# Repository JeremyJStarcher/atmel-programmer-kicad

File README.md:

# atmel-programmer-kicad
ATMEL AT programmer for 8, 14, 20 and 28pin DIP packages

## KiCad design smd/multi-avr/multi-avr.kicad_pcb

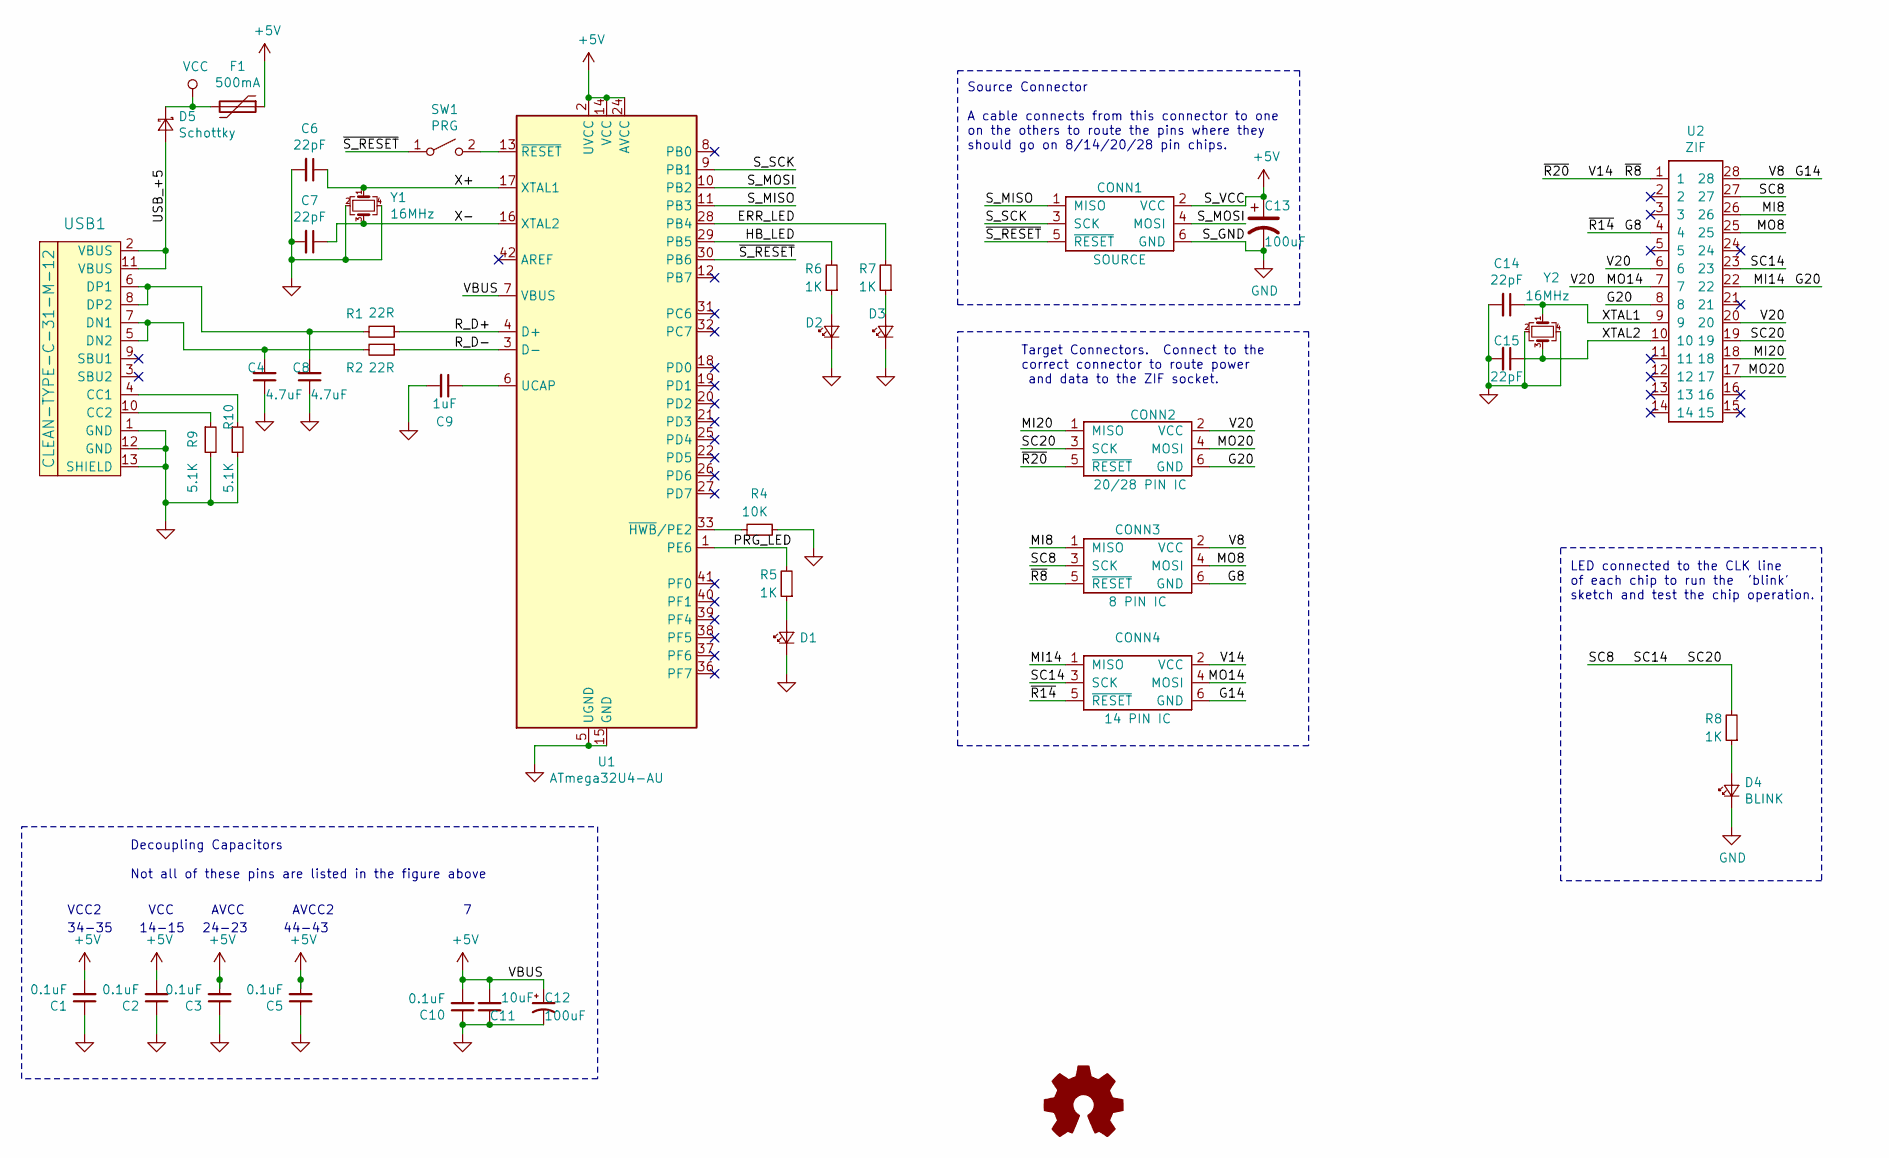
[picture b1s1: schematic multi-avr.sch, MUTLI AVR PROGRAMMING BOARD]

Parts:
C1, C2, C5, C10: 0.1uF; C_0805_2012Metric; JLC C49678
C3: 0.1uF; C_0603_1608Metric; JLC C49678
C4, C8: 4.7uF; C_0805_2012Metric; JLC C1779
C6, C7, C14, C15: 22pF; C_0805_2012Metric; JLC C1804
C9: 1uF; C_0805_2012Metric; JLC C28323
C11: 10uF; C_0805_2012Metric; JLC C15850
C12, C13: 100uF; CP_EIA-3528-15_AVX-H; JLC C16133
CONN1: SOURCE; PinHeader_2x03_P2.54mm_Vertical
CONN2: 20/28 PIN IC; PinHeader_2x03_P2.54mm_Vertical
CONN3: 8 PIN IC; PinHeader_2x03_P2.54mm_Vertical
CONN4: 14 PIN IC; PinHeader_2x03_P2.54mm_Vertical
D1: PRG; LED_0805_2012Metric; JLC C34499
D2: HB; LED_0805_2012Metric; JLC C2296
D3: ERR; LED_0805_2012Metric; JLC C84256
D4: BLINK; LED_0805_2012Metric; JLC C2293
D5: Schottky; D_SOD-123; JLC C8598
F1: 500mA; Fuse_1206_3216Metric; JLC C163133
R1, R2: 22R; R_0805_2012Metric; JLC C17561
R4: 10K; R_0805_2012Metric; JLC C17414
R5, R6, R7, R8: 1K; R_0805_2012Metric; JLC C17513
R9, R10: 5.1K; R_0805_2012Metric; JLC C27834
SW1: PRG; SW_PUSH_6mm_H4.3mm
U1: ATmega32U4-AU; TQFP-44_10x10mm_P0.8mm; JLC C44854
U2: ZIF; ZIF-28
USB1: CLEAN-TYPE-C-31-M-12; HRO-TYPE-C-31-M-12-HandSoldering
Y1, Y2: 16MHz; Crystal_SMD_3225-4Pin_3.2x2.5mm; JLC C13738

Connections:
+5V: C1.2, C2.2, C3.2, C5.2, C10.2, C11.2, C12.1, C13.1, CONN1.2 (VCC), F1.1, U1.2 (UVCC), U1.7 (VBUS), U1.14 (VCC), U1.24 (AVCC), U1.34 (VCC), U1.44 (AVCC)
/ERR_LED: R7.2, U1.28 (PB4)
/G8: CONN3.6 (GND), CONN4.5 (~RESET), U2.4
/G14: CONN3.2 (VCC), CONN4.6 (GND), U2.28
/G20: CONN2.6 (GND), CONN4.1 (MISO), U2.8, U2.22
/HB_LED: R6.2, U1.29 (PB5)
/MI8: CONN3.1 (MISO), U2.26
/MI20: CONN2.1 (MISO), U2.18
/MO8: CONN3.4 (MOSI), U2.25
/MO14: CONN2.2 (VCC), CONN4.4 (MOSI), U2.6, U2.7, U2.20
/MO20: CONN2.4 (MOSI), U2.17
/PRG_LED: R5.2, U1.1 (PE6)
/R_D+: R1.1, U1.4 (D+)
/R_D-: R2.1, U1.3 (D-)
/SC14: CONN2.3 (SCK), CONN3.3 (SCK), CONN4.3 (SCK), R8.2, U2.19, U2.23, U2.27
/S_MISO: CONN1.1 (MISO), U1.11 (PB3)
/S_MOSI: CONN1.4 (MOSI), U1.10 (PB2)
/S_SCK: CONN1.3 (SCK), U1.9 (PB1)
/USB_+5: D5.2 (A), USB1.2 (VBUS), USB1.11 (VBUS)
/V14: CONN2.5 (~RESET), CONN3.5 (~RESET), CONN4.2 (VCC), U2.1
/X+: C6.1, U1.17 (XTAL1), Y1.1
/X-: C7.1, U1.16 (XTAL2), Y1.3
/XTAL1: C14.1, U2.9, Y2.1
/XTAL2: C15.1, U2.10, Y2.3
/~S_RESET: CONN1.5 (~RESET), SW1.1 (A), U1.30 (PB6)
GND: C1.1, C2.1, C3.1, C4.1, C5.1, C6.2, C7.2, C8.1, C9.2, C10.1, C11.1, C12.2, C13.2, C14.2, C15.2, CONN1.6 (GND), D1.1 (K), D2.1 (K), D3.1 (K), D4.1 (K), R4.2, R9.2, R10.2, U1.5 (UGND), U1.15 (GND), U1.23 (GND), U1.35 (GND), U1.43 (GND), USB1.1 (GND), USB1.12 (GND), USB1.13 (SHIELD), Y1.2, Y1.4, Y2.2, Y2.4
unnamed: C4.2, R2.2, USB1.5 (DN2), USB1.7 (DN1)
unnamed: C8.2, R1.2, USB1.6 (DP1), USB1.8 (DP2)
unnamed: C9.1, U1.6 (UCAP)
unnamed: D1.2 (A), R5.1
unnamed: D2.2 (A), R6.1
unnamed: D3.2 (A), R7.1
unnamed: D4.2 (A), R8.1
unnamed: R4.1, U1.33 (~HWB~/PE2)
unnamed: R9.1, USB1.10 (CC2)
unnamed: R10.1, USB1.4 (CC1)
unnamed: SW1.2 (B), U1.13 (~RESET)
VCC: D5.1 (K), F1.2

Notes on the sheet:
14-15
24-23
34-35
44-43
VCC
AVCC
VCC2
AVCC2
Source Connector A cable connects from this connector to one on the others to route the pins where they should go on 8/14/20/28 pin chips.
Target Connectors. Connect to the correct connector to route power and data to the ZIF socket.
LED connected to the CLK line of each chip to run the 'blink' sketch and test the chip operation.
Decoupling Capacitors Not all of these pins are listed in the figure above

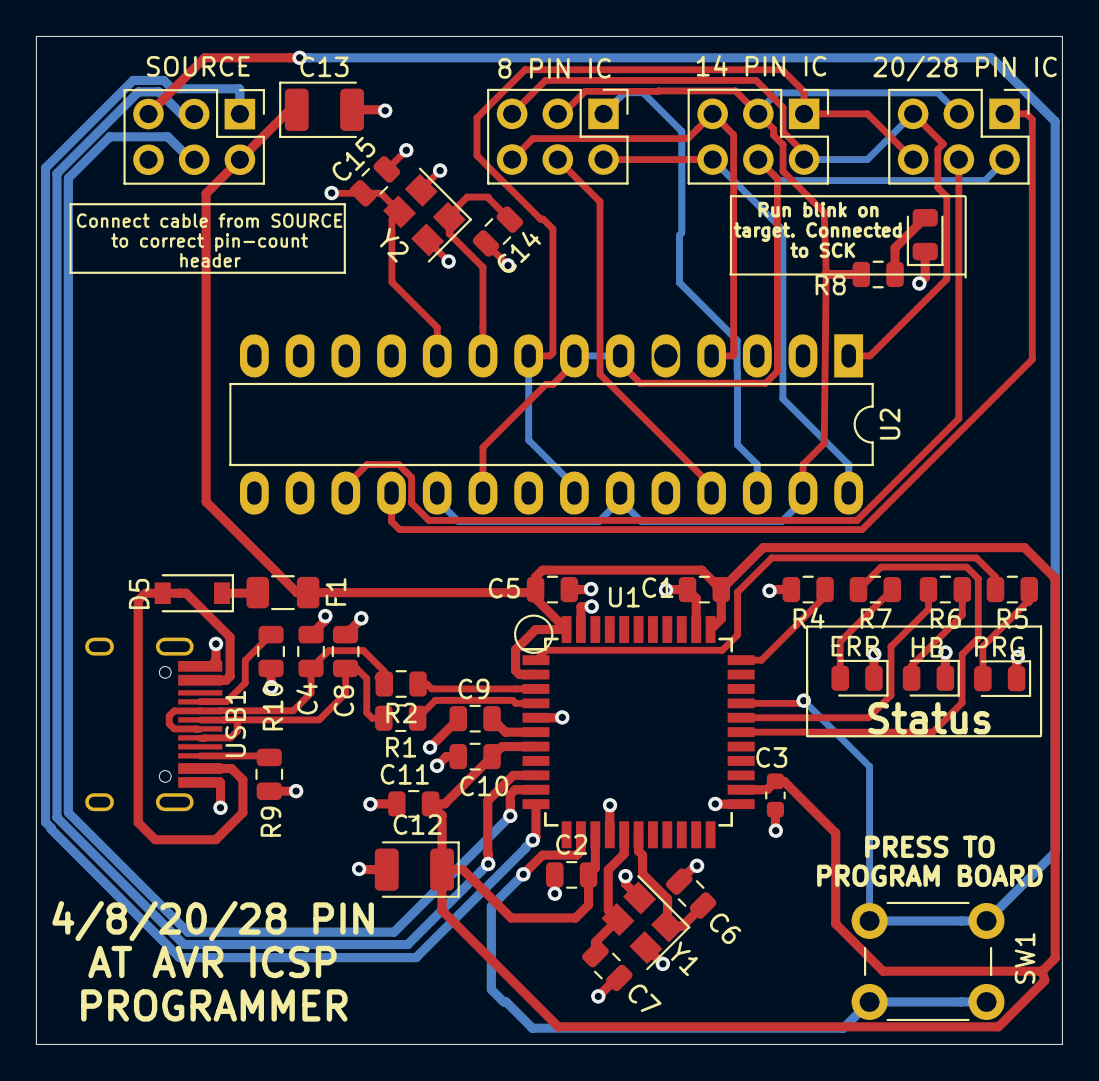
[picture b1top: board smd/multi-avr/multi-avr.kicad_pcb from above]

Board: 2 copper layers, 57.0 x 56.0 mm, 40 parts (0 on the bottom side), 38 nets.

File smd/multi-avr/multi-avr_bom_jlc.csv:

"Comment","Designator","Footprint","LCSC Part #"
"0.1uF","C2,C1,C5,C10","C_0805_2012Metric","C49678"
"0.1uF","C3","C_0603_1608Metric","C49678"
"22pF","C6,C7,C15,C14","C_0805_2012Metric","C1804"
"4.7uF","C8,C4","C_0805_2012Metric","C1779"
"1uF","C9","C_0805_2012Metric","C28323"
"10uF","C11","C_0805_2012Metric","C15850"
"100uF","C12,C13","CP_EIA-3528-15_AVX-H","C16133"
"PRG","D1","LED_0805_2012Metric","C34499"
"HB","D2","LED_0805_2012Metric","C2296"
"ERR","D3","LED_0805_2012Metric","C84256"
"BLINK","D4","LED_0805_2012Metric","C2293"
"Schottky","D5","D_SOD-123","C8598"
"500mA","F1","Fuse_1206_3216Metric","C163133"
"22R","R2,R1","R_0805_2012Metric","C17561"
"10K","R4","R_0805_2012Metric","C17414"
"1K","R6,R7,R5,R8","R_0805_2012Metric","C17513"
"5.1K","R10,R9","R_0805_2012Metric","C27834"
"ATmega32U4-AU","U1","TQFP-44_10x10mm_P0.8mm","C44854"
"CLEAN-TYPE-C-31-M-12","USB1","HRO-TYPE-C-31-M-12-HandSoldering","C165948"
"16MHz","Y1,Y2","Crystal_SMD_3225-4Pin_3.2x2.5mm","C13738"

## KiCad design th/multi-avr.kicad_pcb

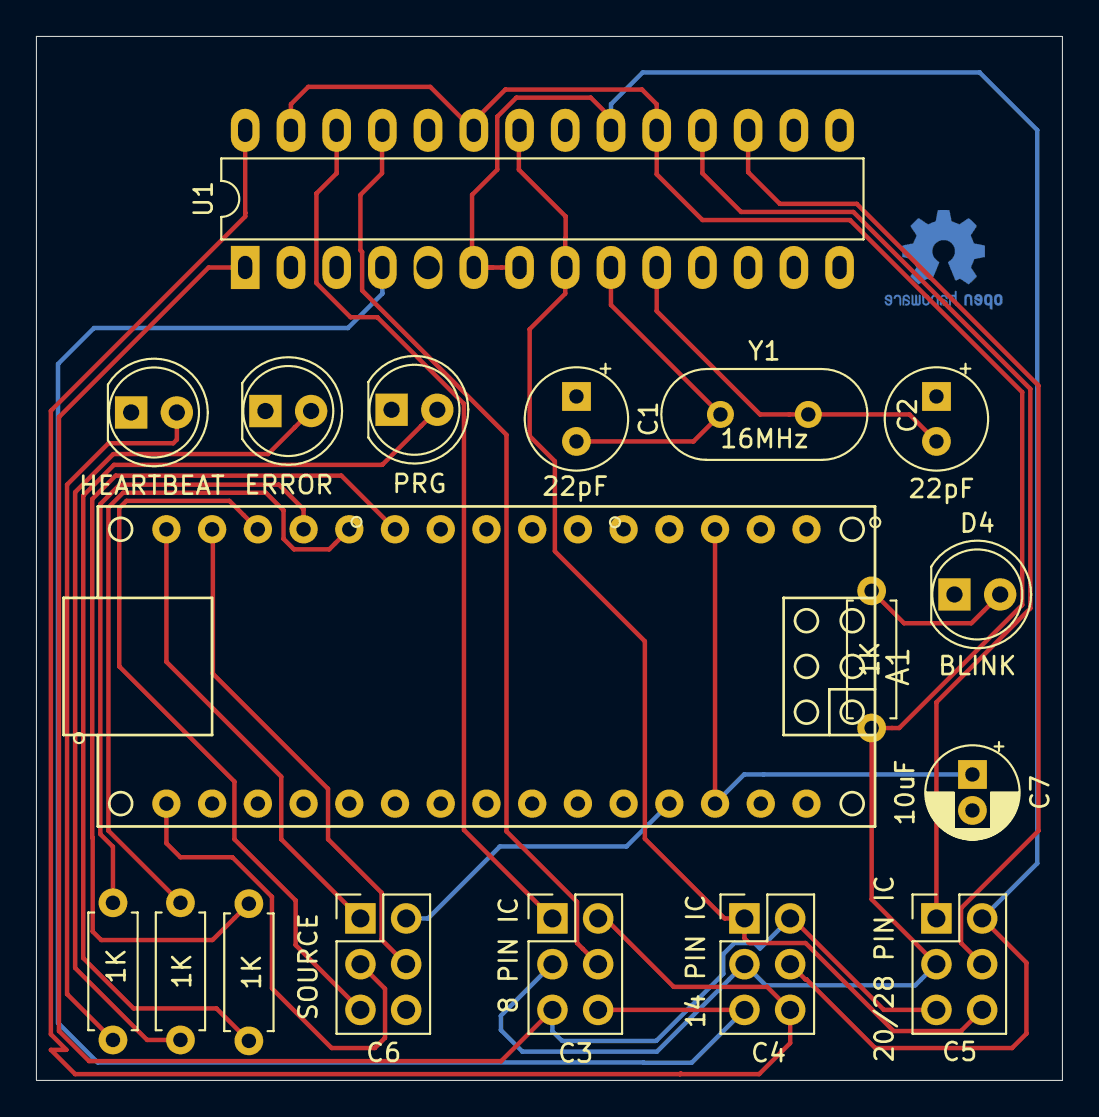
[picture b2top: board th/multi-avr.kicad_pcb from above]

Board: 2 copper layers, 57.0 x 58.0 mm, 18 parts (0 on the bottom side), 26 nets.

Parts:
A1: Arduino_Nano; arduino_nano
C1, C2: 22pF; CP_Radial_Tantal_D5.5mm_P2.50mm
C3: 8 PIN IC; PinHeader_2x03_P2.54mm_Vertical
C4: 14 PIN IC; PinHeader_2x03_P2.54mm_Vertical
C5: 20/28 PIN IC; PinHeader_2x03_P2.54mm_Vertical
C6: SOURCE; PinHeader_2x03_P2.54mm_Vertical
C7: 10uF; CP_Radial_D5.0mm_P2.00mm
D1: HB; LED_D5.0mm_Clear
D2: ERR; LED_D5.0mm_Clear
D3: PRG; LED_D5.0mm_Clear
D4: BLINK; LED_D5.0mm_Clear
R1, R2, R3, R4: 1K; R_Axial_DIN0207_L6.3mm_D2.5mm_P7.62mm_Horizontal
U1: ZIF; ZIF-28
Y1: 16MHz; Crystal_HC49-4H_Vertical

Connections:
/ERR_LED: A1.11, R2.2
/G8: C3.6, C4.5, U1.4
/G14: C3.2, C4.6, U1.28
/G20: C4.1, C5.6, U1.8, U1.22
/HB_LED: A1.12, R1.2
/MI8: C3.1, U1.26
/MI20: C5.1, U1.18
/MO8: C3.4, U1.25
/MO14: C4.4, C5.2, U1.6, U1.7, U1.20
/MO20: C5.4, U1.17
/PRG_LED: A1.10, R3.2
/SC14: C3.3, C4.3, C5.3, R4.2, U1.19, U1.23, U1.27
/S_MISO: A1.15, C6.1
/S_MOSI: A1.14, C6.4
/S_SCK: A1.16, C6.3
/S_VCC: A1.27, C6.2
/V14: C3.5, C4.2, C5.5, U1.1
/~S_RESET: A1.13, C6.5
GND: A1.4, A1.29, C1.1, C2.1, C6.6, C7.2, D1.1, D2.1, D3.1, D4.1
unnamed: A1.3, A1.28, C7.1
unnamed: D1.2, R1.1
unnamed: D2.2, R2.1
unnamed: D3.2, R3.1
unnamed: D4.2, R4.1
XTAL1: C1.2, U1.9, Y1.1
XTAL2: C2.2, U1.10, Y1.2

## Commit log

2020-09-12 Checkin
2020-11-09 Reworked schematic for the USB6 and correct caps
2020-11-12 Added CAD files for a holder for dupont cable ends.
